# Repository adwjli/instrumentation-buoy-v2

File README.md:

# Instrumentation Buoy Data Logger - Version 2

A continuation of the [Instrumentation Buoy Data Logger (Version 1)](https://github.com/andrewjunli/instrumentation-buoy-v1) project, Version 2 features a new PCB layout where the electronics of the Main Board and Power Board are combined into one PCB assembly to make it easier to assemble the buoy. Improvements were made to the solar charging circuitry, a new wireless module has been used and the LED safety light has been redesigned. Also for the first time, I've published the full technical documentation of this design as a learning and reference resource for other hardware designers.

The imagery shown above is a concept design of the new buoy prototype.

## Technical Documentation

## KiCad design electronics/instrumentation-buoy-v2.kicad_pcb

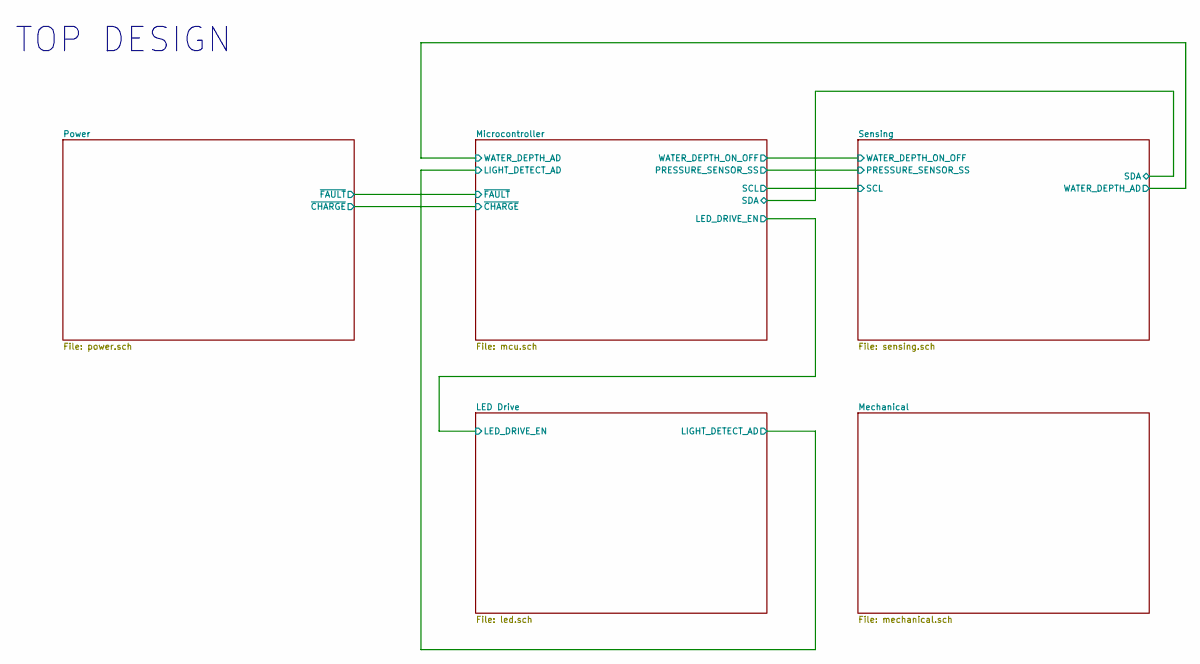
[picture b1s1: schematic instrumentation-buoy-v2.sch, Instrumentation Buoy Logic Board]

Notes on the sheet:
TOP DESIGN

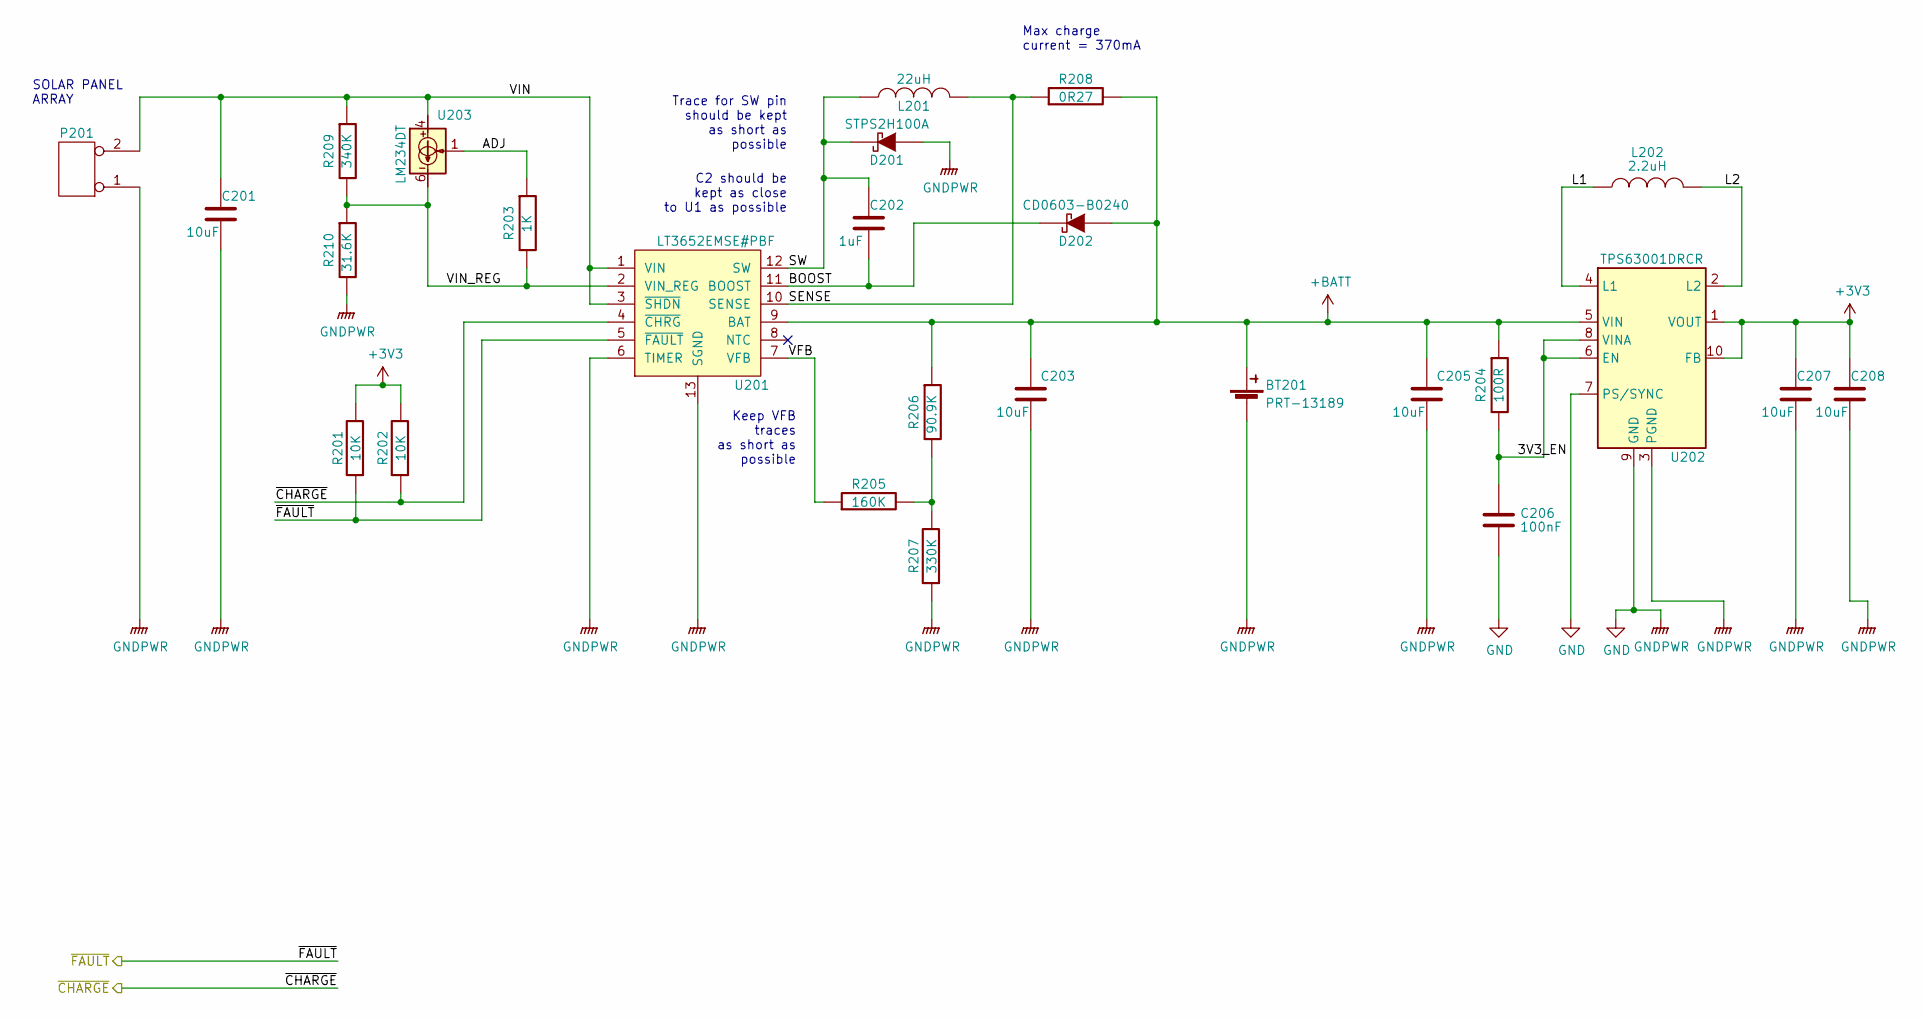
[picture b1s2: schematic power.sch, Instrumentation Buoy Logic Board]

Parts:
BT201: ECS00215; EC18650; Manufacturer Part Number PRT-13189
C201, C203: ECS00053; EC2917; Manfacturer Part Number TPSD106K035R0125
C202: ECS00052; EC0603_C; Manfacturer Part Number GRM188R61H105KAALD
C205, C207, C208: ECS00050; EC0805; Manfacturer Part Number GRM21BR61A106KE19L
C206: ECS00075; EC0603_C; Manfacturer Part Number GRM188R71C104KA01D
D201: ECS00095; ECDO-214AC(SMA); Manufacturer Part Number STPS2H100A
D202: ECS00037; EC0603_DIODE; Manufacturer Part Number CD0603-B0240
L201: ECS00071; ECS00071F; Manufacturer Part Number 46223C
L202: ECS00210; VLS3015CX-2R2M-1; Manufacturer Part Number VLS3015CX-2R2M-1
P201: ECS00004; ECS00004F; Manufacturer Part Number 22-28-4020
R201, R202: ECS00045; EC0603; Manufacturer Part Number ERJ3GEYJ103V
R203: ECS00049; EC0603; Manufacturer Part Number ERJ3EKF1001V
R204: ECS00200; EC0603; Manufacturer Part Number ERJ-3EKF1000V
R205: ECS00119; EC0603; Manufacturer Part Number ERJ-3EKF1603V
R206: ECS00118; EC0603; Manufacturer Part Number ERJ-3EKF9092V
R207: ECS00047; EC0603; Manufacturer Part Number ERJ3EKF3303V
R208: ECS00115; EC1206; Manufacturer Part Number CRL1206-FW-R270ELF
R209: ECS00116; EC0603; Manufacturer Part Number ERJ-3EKF3403V
R210: ECS00117; EC0603; Manufacturer Part Number ERJ-3EKF3162V
U201: ECS00043; ECMSOP-12D; Manufacturer Part Number LT3652EMSE#PBF
U202: ECS00214; Texas_DRC0010J_ThermalVias; Manufacturer Part Number TPS63001DRCR
U203: ECS00212; SOIC127P600X175-8N; Manufacturer Part Number LM234DT

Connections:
+BATT: BT201.1 (+), C203.1, C205.1, D202.1 (A), R204.1, R206.1, R208.2, U201.9 (BAT), U202.5 (VIN); also elsewhere on the board
/Microcontroller/~CHARGE: R202.1, U201.4 (~CHRG); also elsewhere on the board
/Microcontroller/~FAULT: R201.1, U201.5 (~FAULT); also elsewhere on the board
/Power/3V3_EN: C206.1, R204.2, U202.6 (EN), U202.8 (VINA)
/Power/ADJ: R203.1, U203.1
/Power/BOOST: C202.2, D202.2 (K), U201.11 (BOOST)
/Power/L1: L202.1, U202.4 (L1)
/Power/L2: L202.2, U202.2 (L2)
/Power/SENSE: L201.2, R208.1, U201.10 (SENSE)
/Power/SW: C202.1, D201.2 (K), L201.1, U201.12 (SW)
/Power/VFB: R205.1, U201.7 (VFB)
/Power/VIN: C201.1, P201.2 (PM), R209.1, U201.1 (VIN), U201.3 (~SHDN), U203.4
/Power/VIN_REG: R203.2, R209.2, R210.1, U201.2 (VIN_REG), U203.6
GND: BT201.2 (-), C201.2, C203.2, C205.2, C206.2, C207.2, C208.2, D201.1 (A), P201.1, R207.1, R210.2, U201.6 (TIMER), U201.13 (SGND), U202.3 (PGND), U202.7 (PS/SYNC), U202.9 (GND); also elsewhere on the board
unnamed: R205.2, R206.2, R207.2

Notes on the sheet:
Max charge current = 370mA
Trace for SW pin should be kept as short as possible
C2 should be kept as close to U1 as possible
Keep VFB traces as short as possible
SOLAR PANEL ARRAY

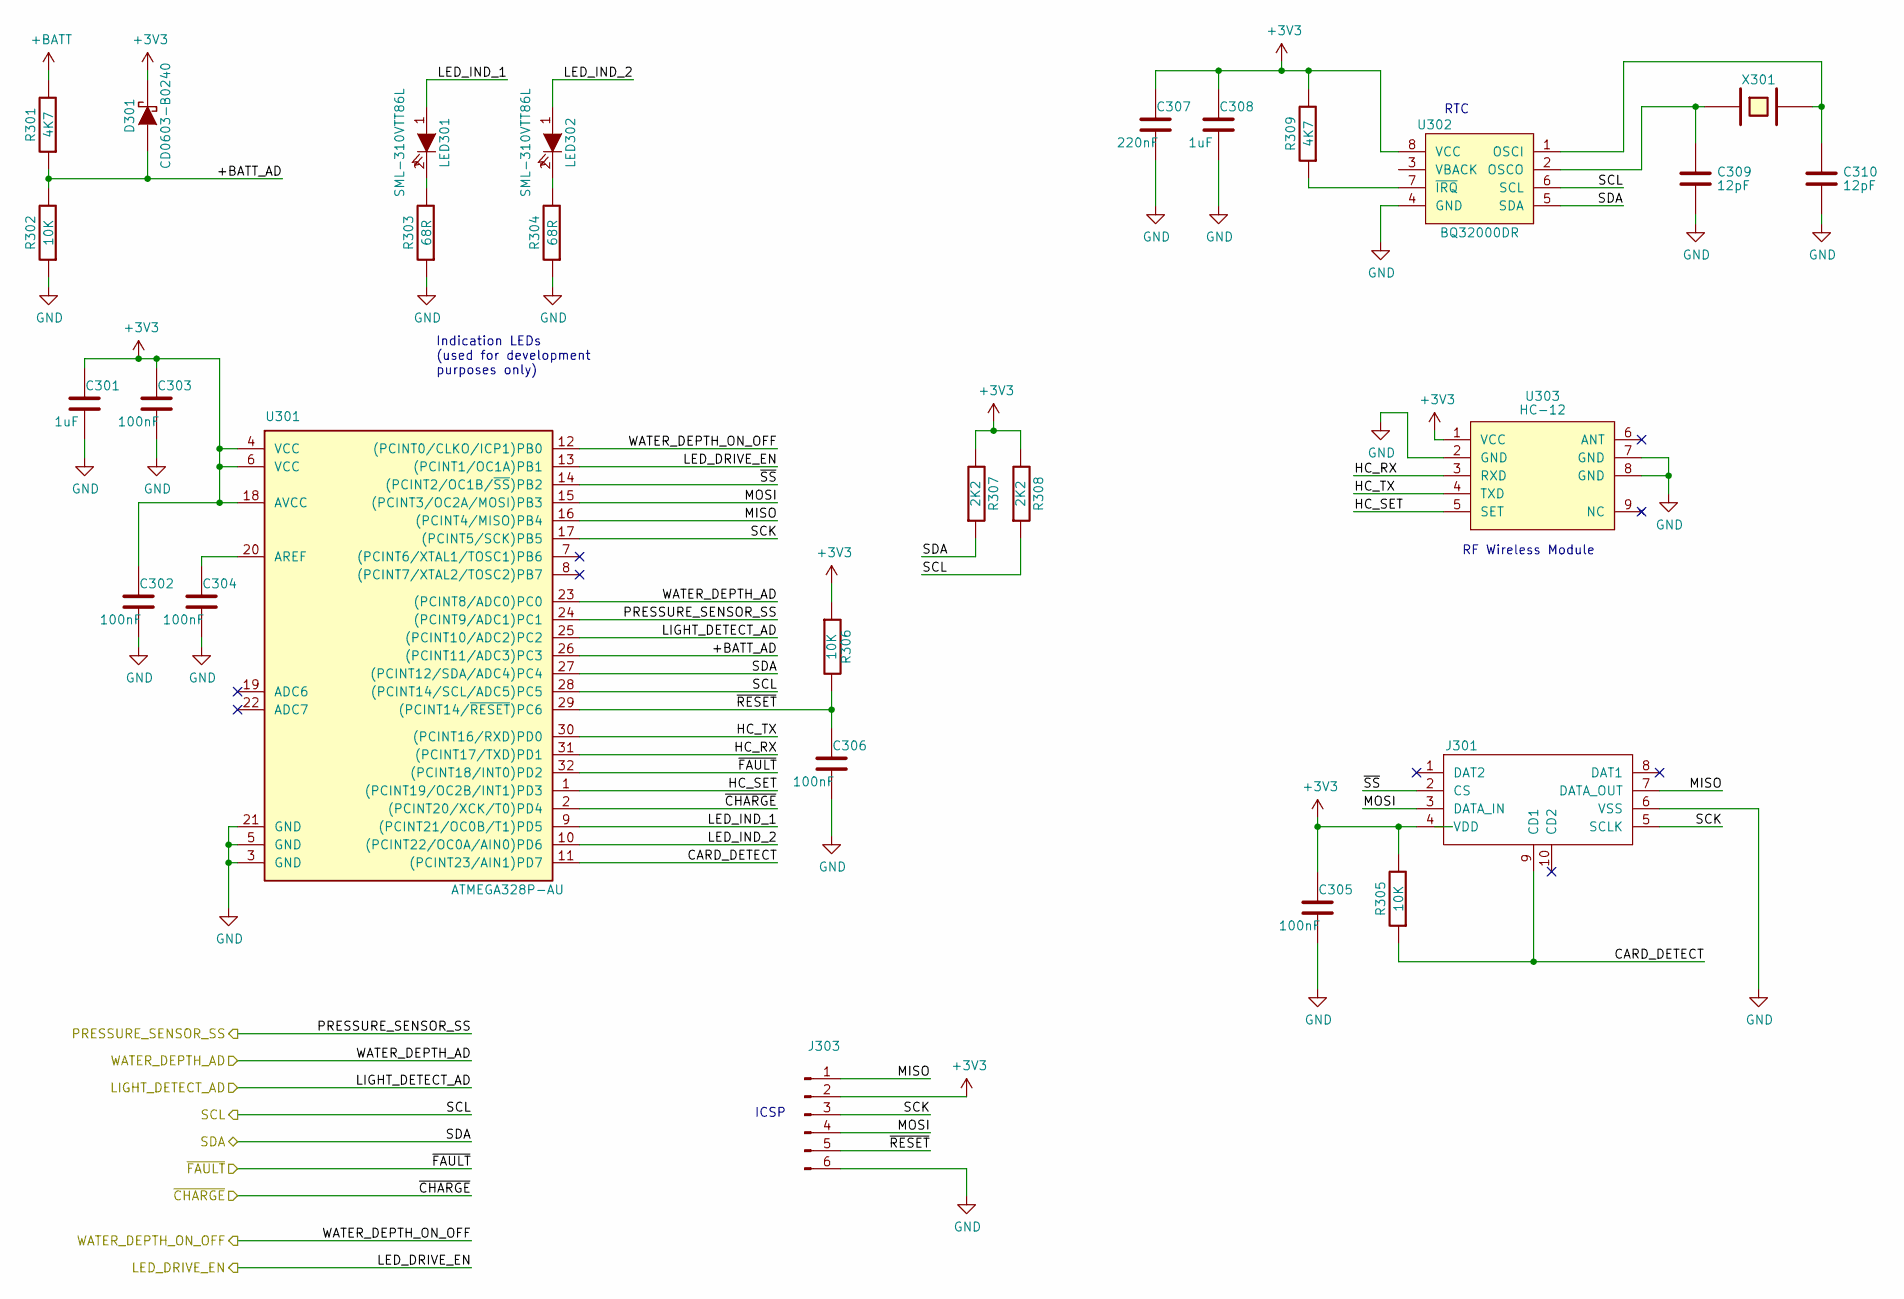
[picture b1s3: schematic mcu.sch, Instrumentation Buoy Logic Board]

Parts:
C301, C308: ECS00052; EC0603_C; Manfacturer Part Number GRM188R61H105KAALD
C302, C303, C304, C305, C306: ECS00075; EC0603_C; Manfacturer Part Number GRM188R71C104KA01D
C307: ECS00078; EC0603_C; Manfacturer Part Number GRM188R71A224KA01D
C309, C310: ECS00204; EC0603_C; Manfacturer Part Number GCM1885C2A120FA16D
D301: ECS00037; EC0603_DIODE; Manufacturer Part Number CD0603-B0240
J301: ECS00065; ECS00065F; Manufacturer Part Number 114-00841-68
J303: CONN6PROG
LED301, LED302: ECS00035; EC0603_LED; Manufacturer Part Number SML-310VTT86L
R301, R309: ECS00086; EC0603; Manufacturer Part Number CR0603-FX-4701ELF
R302, R305, R306: ECS00045; EC0603; Manufacturer Part Number ERJ3GEYJ103V
R303, R304: ECS00081; EC0603; Manufacturer Part Number CR0603-FX-68R0ELF
R307, R308: ECS00084; EC0603; Manufacturer Part Number MC0063W060312K2
U301: ECS00017; ECTQFP-32; Manufacturer Part Number ATMEGA328P-AU
U302: ECS00032; ECSOIC-8; Manufacturer Part Number BQ32000DR
U303: ECA00003; ECA00003F; Manufacturer Part Number HC-12
X301: ECS00005; ECS00005F; Manufacturer Part Number CC4V-T1A 32.768KHZ +-20PPM 9PF

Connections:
+BATT: R301.2; also elsewhere on the board
/LED Drive/LED_DRIVE_EN: U301.13 ((PCINT1/OC1A)PB1); also elsewhere on the board
/LED Drive/LIGHT_DETECT_AD: U301.25 ((PCINT10/ADC2)PC2); also elsewhere on the board
/Microcontroller/+BATT_AD: D301.1 (A), R301.1, R302.2, U301.26 ((PCINT11/ADC3)PC3)
/Microcontroller/CARD_DETECT: J301.9 (CD1), R305.1, U301.11 ((PCINT23/AIN1)PD7)
/Microcontroller/HC_RX: U301.31 ((PCINT17/TXD)PD1), U303.3 (RXD)
/Microcontroller/HC_SET: U301.1 ((PCINT19/OC2B/INT1)PD3), U303.5 (SET)
/Microcontroller/HC_TX: U301.30 ((PCINT16/RXD)PD0), U303.4 (TXD)
/Microcontroller/LED_IND_1: LED301.1 (A), U301.9 ((PCINT21/OC0B/T1)PD5)
/Microcontroller/LED_IND_2: LED302.1 (A), U301.10 ((PCINT22/OC0A/AIN0)PD6)
/Microcontroller/MISO: J301.7 (DATA_OUT), J303.1, U301.16 ((PCINT4/MISO)PB4)
/Microcontroller/MOSI: J301.3 (DATA_IN), J303.4, U301.15 ((PCINT3/OC2A/MOSI)PB3)
/Microcontroller/PRESSURE_SENSOR_SS: U301.24 ((PCINT9/ADC1)PC1); also elsewhere on the board
/Microcontroller/SCK: J301.5 (SCLK), J303.3, U301.17 ((PCINT5/SCK)PB5)
/Microcontroller/SCL: R308.1, U301.28 ((PCINT14/SCL/ADC5)PC5), U302.6 (SCL); also elsewhere on the board
/Microcontroller/SDA: R307.1, U301.27 ((PCINT12/SDA/ADC4)PC4), U302.5 (SDA); also elsewhere on the board
/Microcontroller/WATER_DEPTH_AD: U301.23 ((PCINT8/ADC0)PC0); also elsewhere on the board
/Microcontroller/WATER_DEPTH_ON_OFF: U301.12 ((PCINT0/CLKO/ICP1)PB0); also elsewhere on the board
/Microcontroller/~CHARGE: U301.2 ((PCINT20/XCK/T0)PD4); also elsewhere on the board
/Microcontroller/~FAULT: U301.32 ((PCINT18/INT0)PD2); also elsewhere on the board
/Microcontroller/~RESET: C306.1, J303.5, R306.2, U301.29 ((PCINT14/~RESET~)PC6)
/Microcontroller/~SS: J301.2 (CS), U301.14 ((PCINT2/OC1B/~SS~)PB2)
GND: C301.2, C302.2, C303.2, C304.2, C305.2, C306.2, C307.2, C308.2, C309.2, C310.2, J301.6 (VSS), J303.6, R302.1, R303.1, R304.1, U301.3 (GND), U301.5 (GND), U301.21 (GND), U302.4 (GND), U303.2 (GND), U303.7 (GND), U303.8 (GND); also elsewhere on the board
unnamed: C304.1, U301.20 (AREF)
unnamed: C309.1, U302.2 (OSCO), X301.1
unnamed: C310.1, U302.1 (OSCI), X301.2
unnamed: LED301.2 (K), R303.2
unnamed: LED302.2 (K), R304.2
unnamed: R309.1, U302.7 (~IRQ)

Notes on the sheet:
RTC
RF Wireless Module
ICSP
Indication LEDs (used for development purposes only)

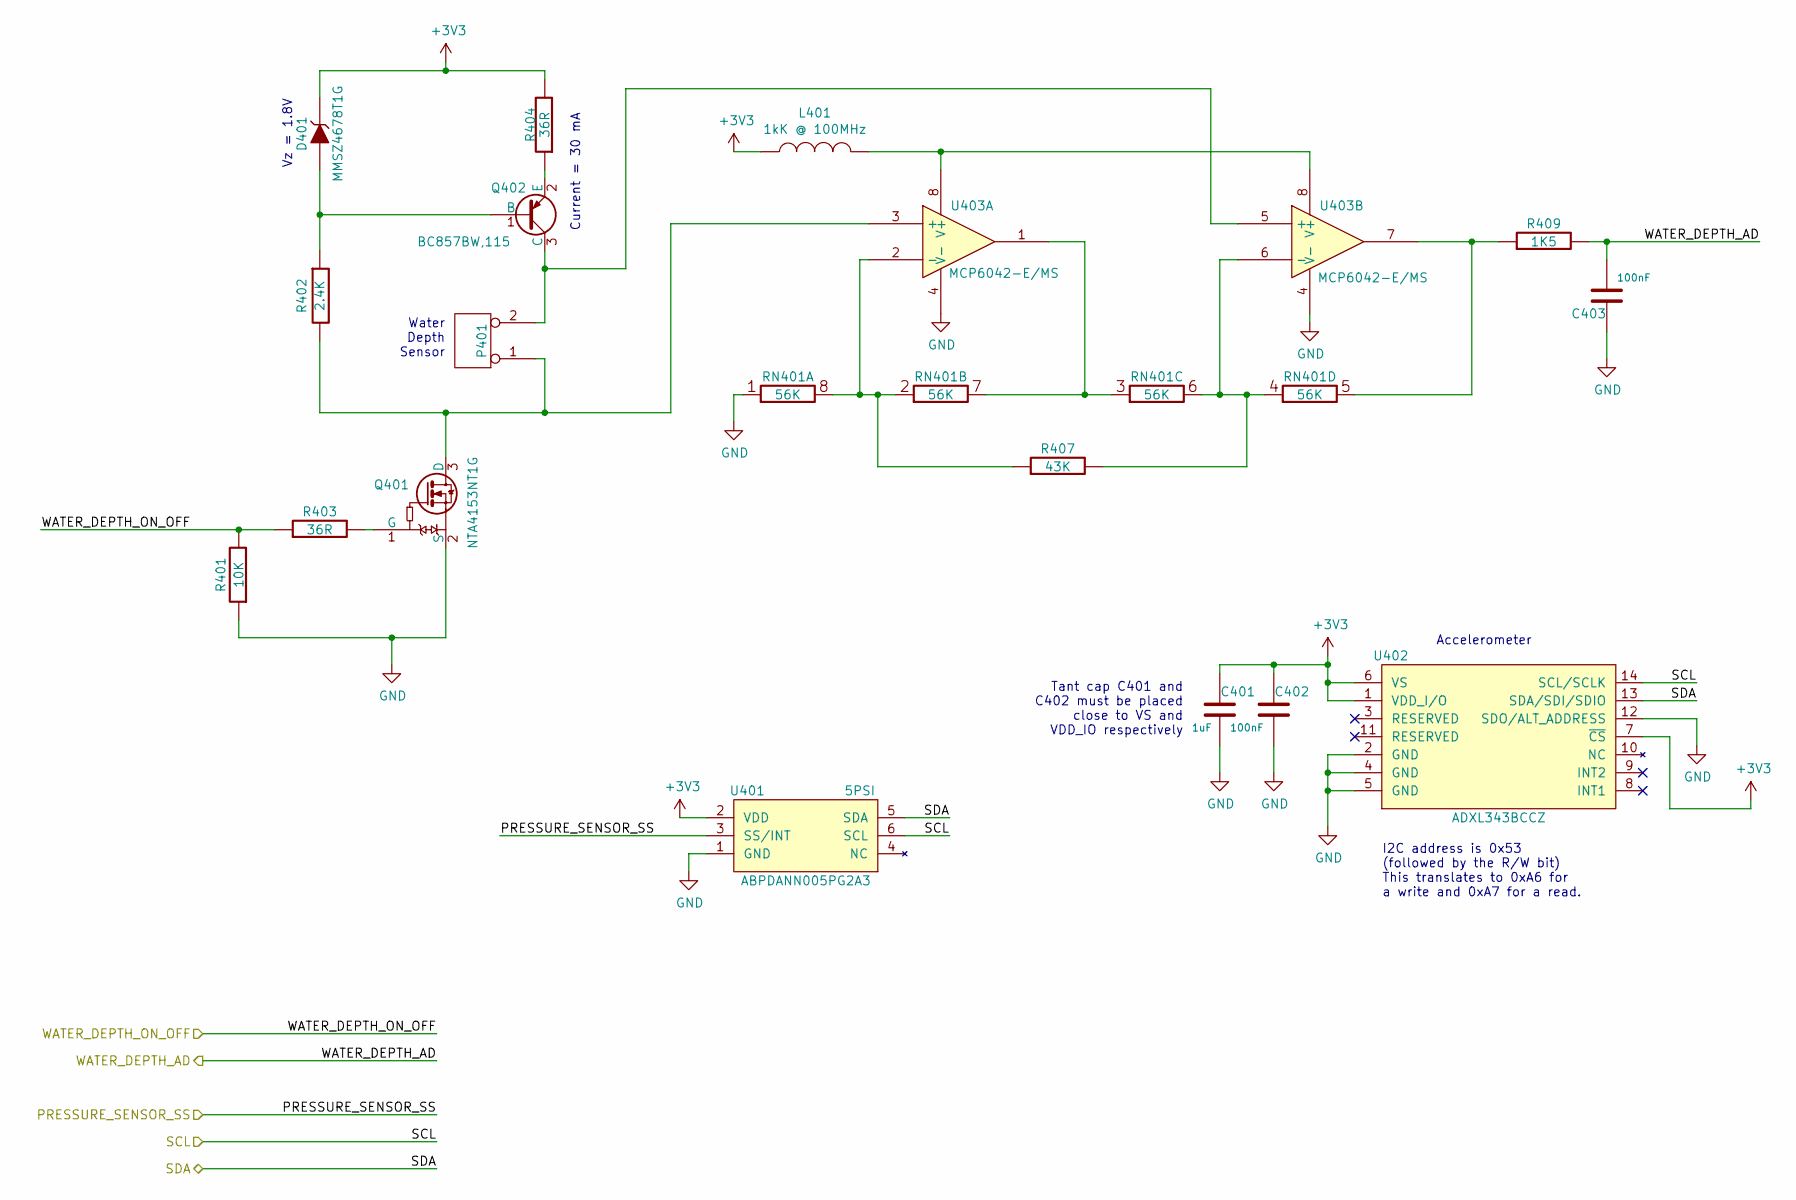
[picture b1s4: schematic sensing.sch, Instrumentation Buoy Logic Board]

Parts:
C401: ECS00052; EC0603_C; Manfacturer Part Number GRM188R61H105KAALD
C402, C403: ECS00075; EC0603_C; Manfacturer Part Number GRM188R71C104KA01D
D401: ECS00072; ECS00072F; Manufacturer Part Number MMSZ4678T1G
L401: ECS00074; EC0603_L; Manufacturer Part Number BLM18TG102TN1D
P401: ECS00067; ECS00067F; Manufacturer Part Number B2B-PH-SM4-TB(LF)(SN)
Q401: ECS00087; ECSOT416; Manufacturer Part Number NTA4153NT1G
Q402: ECS00073; ECSOT323; Manufacturer Part Number BC857BW,115
R401: ECS00045; EC0603; Manufacturer Part Number ERJ3GEYJ103V
R402: ECS00201; EC0603; Manufacturer Part Number ERJ-3EKF2401V
R403, R404: ECS00080; EC0603; Manufacturer Part Number CRCW060336R0FKEA
R407: ECS00203; EC0603; Manufacturer Part Number ERJ-3EKF4302V
R409: ECS00083; EC0603; Manufacturer Part Number CR0603-FX-1501ELF
RN401: ECS00206; ECS00206F; Manufacturer Part Number TC164-FR-0756KL
U401: ECS00114; ECS00114F; Manufacturer Part Number ABPDANN005PG2A3
U402: ECS00016; ECS00016F; Manufacturer Part Number ADXL343BCCZ
U403: ECS00030; ECMSOP-8; Manufacturer Part Number MCP6042-E/MS

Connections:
/Microcontroller/PRESSURE_SENSOR_SS: U401.3 (SS/INT); also elsewhere on the board
/Microcontroller/SCL: U401.6 (SCL), U402.14 (SCL/SCLK); also elsewhere on the board
/Microcontroller/SDA: U401.5 (SDA), U402.13 (SDA/SDI/SDIO); also elsewhere on the board
/Microcontroller/WATER_DEPTH_AD: C403.2, R409.2; also elsewhere on the board
/Microcontroller/WATER_DEPTH_ON_OFF: R401.2, R403.1; also elsewhere on the board
GND: C401.2, C402.2, C403.1, Q401.2 (S), R401.1, RN401.1, U401.1 (GND), U402.2 (GND), U402.4 (GND), U402.5 (GND), U402.12 (SDO/ALT_ADDRESS), U403.4 (V-); also elsewhere on the board
unnamed: D401.2 (A), Q402.1 (B), R402.1
unnamed: L401.2, U403.8 (V+)
unnamed: P401.1, Q401.3 (D), R402.2, U403.3 (+)
unnamed: P401.2 (PM), Q402.3 (C), U403.5 (+)
unnamed: Q401.1 (G), R403.2
unnamed: Q402.2 (E), R404.1
unnamed: R407.1, RN401.2, RN401.8, U403.2 (-)
unnamed: R407.2, RN401.4, RN401.6, U403.6 (-)
unnamed: R409.1, RN401.5, U403.7
unnamed: RN401.3, RN401.7, U403.1

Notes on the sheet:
Accelerometer
I2C address is 0x53 (followed by the R/W bit) This translates to 0xA6 for a write and 0xA7 for a read.
Water Depth Sensor
Vz = 1.8V
Current = 30 mA
Tant cap C401 and C402 must be placed close to VS and VDD_IO respectively

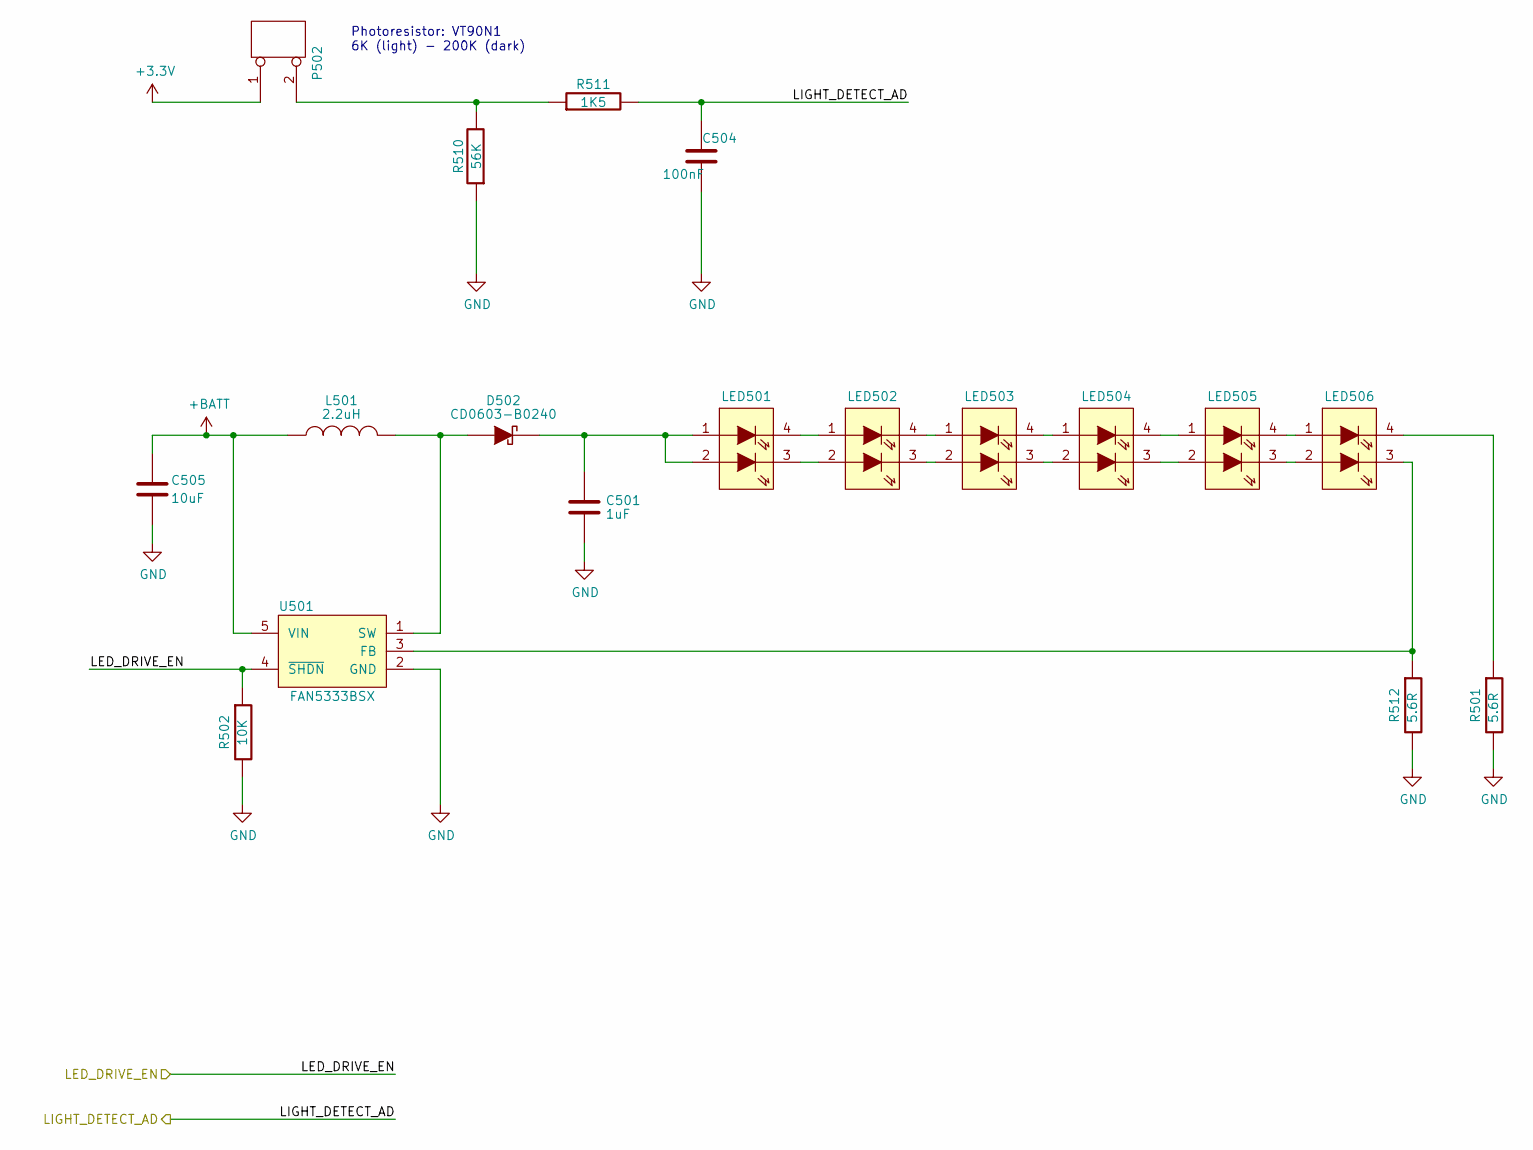
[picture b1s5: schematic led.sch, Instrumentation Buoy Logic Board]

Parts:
C501: ECS00052; EC0603_C; Manfacturer Part Number GRM188R61H105KAALD
C504: ECS00075; EC0603_C; Manfacturer Part Number GRM188R71C104KA01D
C505: ECS00051; EC1206; Manfacturer Part Number GRM31CR61H106KA12L
D502: ECS00037; EC0603_DIODE; Manufacturer Part Number CD0603-B0240
L501: ECS00210; VLS3015CX-2R2M-1; Manufacturer Part Number VLS3015CX-2R2M-1
LED501, LED502, LED503, LED504, LED505, LED506: ECS00208; CLV1A-FKB; Manufacturer Part Number CLA2A-WKW-CYBZ0343TR-ND
P502: ECS00004; ECS00004F; Manufacturer Part Number 22-28-4020
R501, R512: ECS00213; EC0603; Manufacturer Part Number ERJ-3RQF5R6V
R502: ECS00045; EC0603; Manufacturer Part Number ERJ3GEYJ103V
R510: ECS00085; EC0603; Manufacturer Part Number CRCW060356K0FKEAHP
R511: ECS00083; EC0603; Manufacturer Part Number CR0603-FX-1501ELF
U501: ECS00207; ECSOT23-5; Manufacturer Part Number FAN5333BSX

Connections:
+BATT: C505.1, L501.1, U501.5 (VIN); also elsewhere on the board
/LED Drive/LED_DRIVE_EN: R502.1, U501.4 (~SHDN); also elsewhere on the board
/LED Drive/LIGHT_DETECT_AD: C504.1, R511.2; also elsewhere on the board
GND: C501.2, C504.2, C505.2, R501.2, R502.2, R510.1, R512.2, U501.2 (GND); also elsewhere on the board
unnamed: C501.1, D502.2 (K), LED501.1 (A), LED501.2 (A)
unnamed: D502.1 (A), L501.2, U501.1 (SW)
unnamed: LED501.3 (K), LED502.2 (A)
unnamed: LED501.4 (K), LED502.1 (A)
unnamed: LED502.3 (K), LED503.2 (A)
unnamed: LED502.4 (K), LED503.1 (A)
unnamed: LED503.3 (K), LED504.2 (A)
unnamed: LED503.4 (K), LED504.1 (A)
unnamed: LED504.3 (K), LED505.2 (A)
unnamed: LED504.4 (K), LED505.1 (A)
unnamed: LED505.3 (K), LED506.2 (A)
unnamed: LED505.4 (K), LED506.1 (A)
unnamed: LED506.3 (K), R512.1, U501.3 (FB)
unnamed: LED506.4 (K), R501.1
unnamed: P502.2 (PM), R510.2, R511.1

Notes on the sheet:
Photoresistor: VT90N1 6K (light) - 200K (dark)

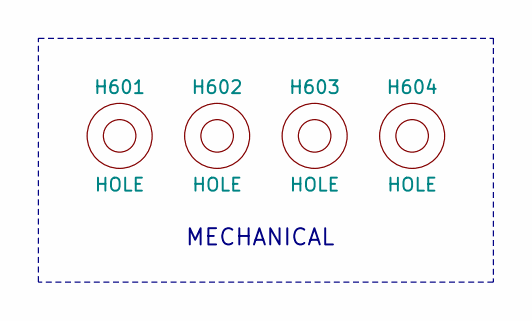
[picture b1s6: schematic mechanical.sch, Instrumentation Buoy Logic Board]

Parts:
H601, H602, H603, H604: HOLE; HOLE_5.5MM

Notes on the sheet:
MECHANICAL

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
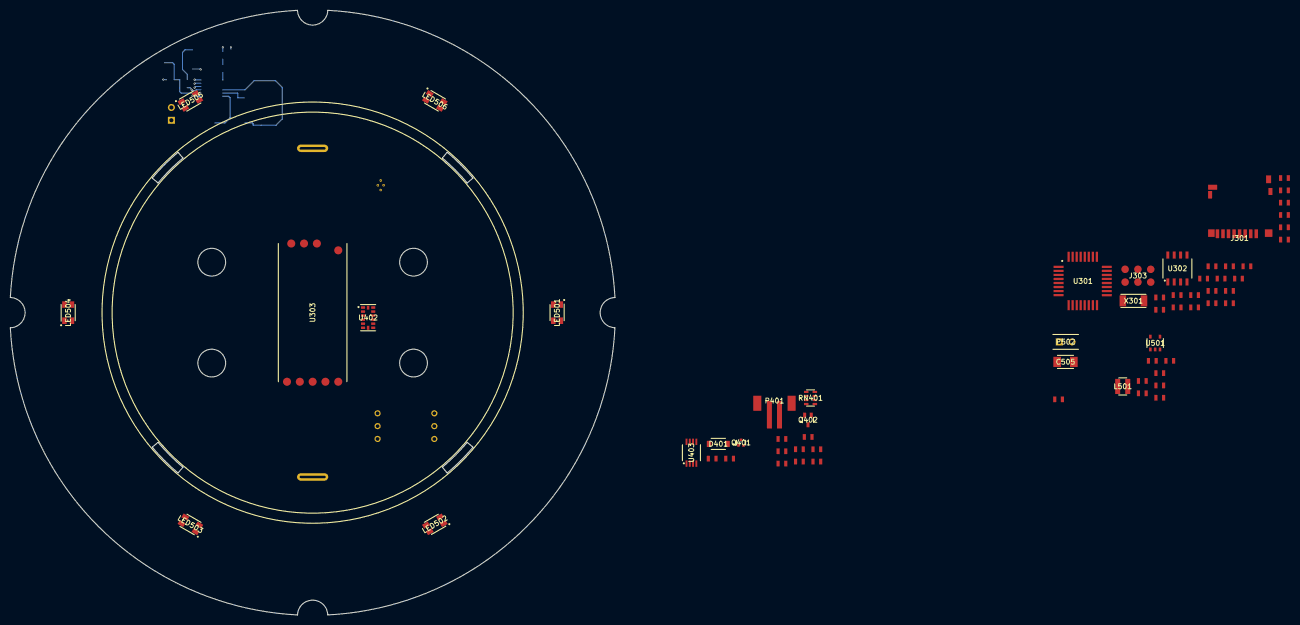
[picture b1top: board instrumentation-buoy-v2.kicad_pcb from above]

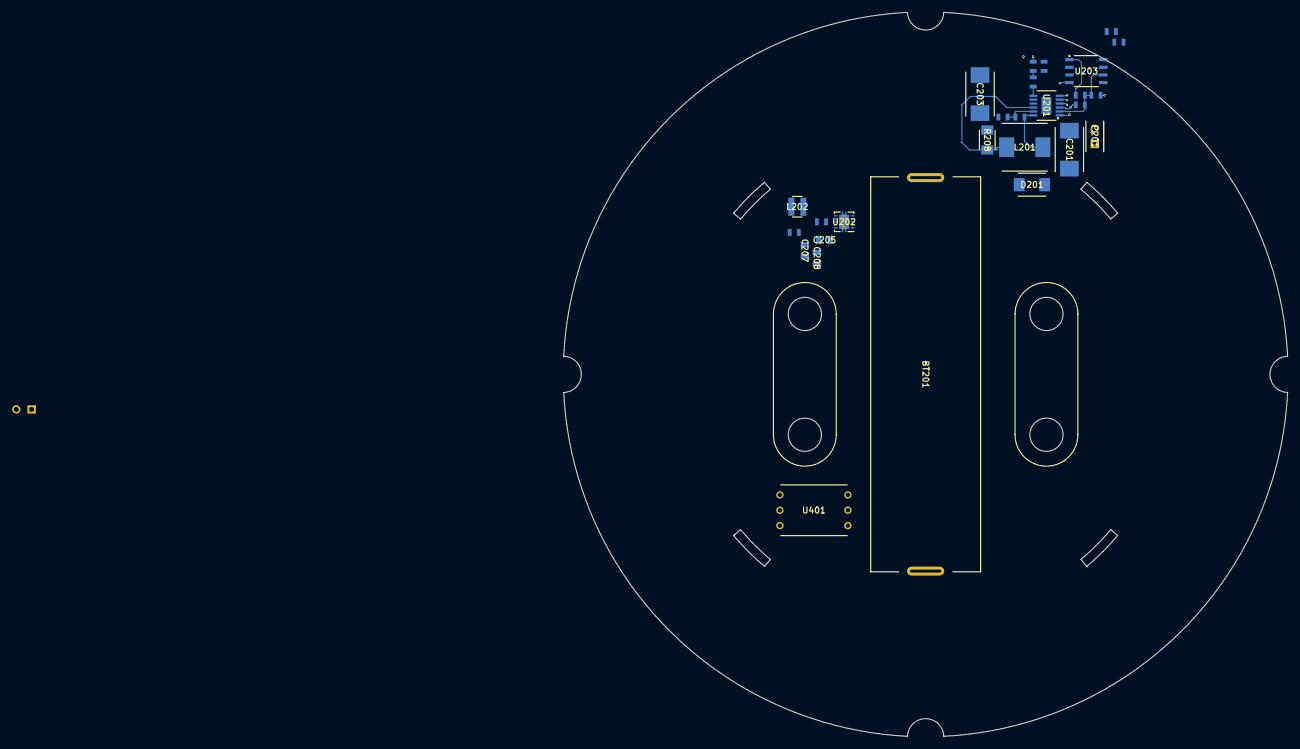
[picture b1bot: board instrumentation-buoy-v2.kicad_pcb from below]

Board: 4 copper layers, 119.9 x 119.8 mm, 94 parts (27 on the bottom side), 66 nets.

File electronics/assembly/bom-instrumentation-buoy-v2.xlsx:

Reference | Internal Part Number | Quantity | Component Value | Manufacturer | Manufacturer Part Number | Part Description
BT201 | ECS00215 | 1 | 3.7V | SparkFun Electronics | PRT-13189 | BATTERY LITHIUM 3.7V 2.6AH
C202 C301 C308 C401 C501 | ECS00052 | 5 | 1uF | Murata | GRM188R61H105KAALD | 1uF, 0603, 10%, 50V, X5R, Ceramic
C203 C201 | ECS00053 | 2 | 10uF | AVX | TPSD106K035R0125 | 10uF, 2917, 10%, 35V, Tantalum
C205 C208 C207 | ECS00050 | 3 | 10uF | Murata | GRM21BR61A106KE19L | 10uF, 0805, 10%, 10V, X5R, Ceramic
C206 C303 C302 C304 C306 C305 C403 C402 C504 | ECS00075 | 9 | 100nF | Murata | GRM188R71C104KA01D | 100nF, 0603, 10%, 16V, X7R, Ceramic
C307 | ECS00078 | 1 | 220nF | Murata | GRM188R71A224KA01D | 220nF, 0603, 10%, 10V, X7R, Ceramic
C309 C310 | ECS00204 | 2 | 12pF | Murata | GCM1885C2A120FA16D | 12pF ¬±1% 100V Ceramic Capacitor C0G, NP0 0603 (1608 Metric)
C505 | ECS00051 | 1 | 10uF | Murata | GRM31CR61H106KA12L | 10uF, 1206, 10%, 50V, X5R, Ceramic
D201 | ECS00095 | 1 |  | ST Microelectronics | STPS2H100A | Schottky, Single, 2A, SMD
D202 D301 D502 | ECS00037 | 3 |  | Bourns | CD0603-B0240 | Schottky, Single, 0.1A, SMD
D401 | ECS00072 | 1 | 1.8V | On Semiconductor | MMSZ4678T1G | Zener, 1.8V, 0.25W, SMD
J301 | ECS00065 | 1 |  | Amphenol Commercial Products | 114-00841-68 | Micro SD Card Holder, SMD
L201 | ECS00071 | 1 | 22uH | Murata | 46223C | 22uH, 1.8A, 0R12
L202 L501 | ECS00210 | 2 | 2.2uH | TDK | VLS3015CX-2R2M-1 | IND PWR CIR WOUND FERRITE MATERI
L401 | ECS00074 | 1 | 1kK @ 100MHz | Murata | BLM18TG102TN1D | 1K @ 100MHz, 0603, 0.1A, 0R6
LED301 LED302 | ECS00035 | 2 | Red | Rohm | SML-310VTT86L | Red, 4mcd, 0603
LED501 LED503 LED505 LED506 LED502 LED504 | ECS00208 | 6 | White | Cree Inc. | CLA2A-WKW-CYBZ0343TR-ND | LED COOL WHITE DIFF 4PLCC SMD
P201 P502 | ECS00004 | 2 | 2x1 | Molex | 22-28-4020 | 2-way, header, 2.54mm pitch, vertical, through hole, KK Series
P401 | ECS00067 | 1 | 2x1 | JST | B2B-PH-SM4-TB(LF)(SN) | 2-way, header, 2mm pitch, vertical, SMD, PH Series
Q401 | ECS00087 | 1 |  | On Semiconductor | NTA4153NT1G | MOSFET, N-Channel, 0.915A, 0R127
Q402 | ECS00073 | 1 |  | NXP | BC857BW,115 | BJT, PNP, 45V, 0.1A
R202 R201 R302 R305 R306 R401 R502 | ECS00045 | 7 | 10K | Panasonic | ERJ3GEYJ103V | 10K, 0603, 5%, 0.1W, Thick Film
R203 | ECS00049 | 1 | 1K | Panasonic | ERJ3EKF1001V | 1K, 0603, 1%, 0.1W, Thick Film
R204 | ECS00200 | 1 | 100R | Panasonic | ERJ-3EKF1000V | 100 Ohms ¬±1% 0.1W, 1/10W Chip Resistor 0603 (1608 Metric) Automotive AEC-Q200 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
R205 | ECS00119 | 1 | 160K | Panasonic | ERJ-3EKF1603V | 160 kOhms ¬±1% 0.1W, 1/10W Chip Resistor 0603 (1608 Metric) Automotive AEC-Q200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
R206 | ECS00118 | 1 | 90.9K | Panasonic | ERJ-3EKF9092V | 90.9 kOhms ¬±1% 0.1W, 1/10W Chip Resistor 0603 (1608 Metric) Automotive AEC-Q20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
R207 | ECS00047 | 1 | 330K | Panasonic | ERJ3EKF3303V | 330K, 0603, 1%, 0.1W, Thick Film
R208 | ECS00115 | 1 | 0R27 | Bourns | CRL1206-FW-R270ELF | RES 0.27 OHM 1% 1/4W 1206
R209 | ECS00116 | 1 | 340K | Panasonic | ERJ-3EKF3403V | 340 kOhms ¬±1% 0.1W, 1/10W Chip Resistor 0603 (1608 Metric) Automotive AEC-Q200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
R210 | ECS00117 | 1 | 31.6K | Panasonic | ERJ-3EKF3162V | RES SMD 31.6K OHM 1% 1/10W 0603
R301 R309 | ECS00086 | 2 | 4K7 | Bourns | CR0603-FX-4701ELF | 4K7, 0603, 1%, 0.063W, Thick Film
R303 R304 | ECS00081 | 2 | 68R | Bourns | CR0603-FX-68R0ELF | 68R, 0603, 1%, 0.1W, Thick Film
R308 R307 | ECS00084 | 2 | 2K2 | Multicomp | MC0063W060312K2 | 2K2, 0603, 1%, 0.063W, Thick Film
R402 | ECS00201 | 1 | 2.4K | Panasonic | ERJ-3EKF2401V | RES SMD 2.4K OHM 1% 1/10W 0603
R404 R403 | ECS00080 | 2 | 36R | Vishay | CRCW060336R0FKEA | 36R, 0603, 0.1W, Thick Film
R407 | ECS00203 | 1 | 43K | Panasonic | ERJ-3EKF4302V | RES SMD 43K OHM 1% 1/10W 0603
R409 R511 | ECS00083 | 2 | 1K5 | Bourns | CR0603-FX-1501ELF | 1K5, 0603, 1%, 0.1W, Thick Film
R510 | ECS00085 | 1 | 56K | Vishay | CRCW060356K0FKEAHP | 56K, 0603, 1%, 0.25W, Thick Film, High Power
R512 R501 | ECS00213 | 2 | 5.6R | Panasonic | ERJ-3RQF5R6V | RES SMD 5.6 OHM 1% 1/10W 0603
RN401 | ECS00206 | 1 | 56K | Yageo | TC164-FR-0756KL | RES ARRAY 4 RES 56K OHM 1206
U201 | ECS00043 | 1 |  | Linear Technology | LT3652EMSE#PBF | Switch Mode Charge Controller with MPPT
U202 | ECS00214 | 1 |  | Texas Instruments | TPS63001DRCR | IC REG BCK BST 3.3V 1.6A 10VSON
U203 | ECS00212 | 1 |  | ST Microelectronics | LM234DT | IC CURRENT SOURCE 3% 8SOIC
U301 | ECS00017 | 1 |  | Atmel | ATMEGA328P-AU | ATMega328P, TQFP
U302 | ECS00032 | 1 |  | Texas Instruments | BQ32000DR | RTC, 8SOIC
U303 | ECA00003 | 1 |  | HC | HC-12 | HC-12 Wireless UART Serial Data Module
U401 | ECS00114 | 1 | 5PSI | Honeywell | ABPDANN005PG2A3 | Pressure Sensor, Amplified, 5 psi, Digital, Gauge, 3.3 VDC, Single Axial Barbed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
U402 | ECS00016 | 1 |  | Analog Device | ADXL343BCCZ | Accelerometer, 3 axis
U403 | ECS00030 | 1 |  | Microchip | MCP6042-E/MS | Dual Package, 8-MSOP, Unity Gain Stable
U501 | ECS00207 | 1 |  | ON Semiconductor | FAN5333BSX | IC LED DRIVER RGLTR DIM SOT23-5
X301 | ECS00005 | 1 | 32.768kHz | Micro Crystal Switzerland | CC4V-T1A 32.768KHZ +-20PPM 9PF | Crystal, 32.768kHz, 20ppm, 9pF, SMD

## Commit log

2020-05-15 First commit.
2020-05-25 Updating README.md for v2.
2020-05-25 Commiting the technical documentation for Instrumentation Buoy V2.
2020-05-25 Commiting BOM and updated .gitignore file.
2020-05-25 Adding schematic jpg files, updated BOM and added BOM to README markdown as well. Updated top level README to formate the tecnical documentation better.
2020-05-25 Updating documentation.
2020-05-25 Fixed typo in README.md.
2020-05-25 Updating README.md.
2020-05-25 Adding buoy-concept.png.
